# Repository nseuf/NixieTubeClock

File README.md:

# NixieTubeClock
NixieTubeClock is a GPS-based desk clock that is precise up to 10ms, and uses nixie tubes to display the time.

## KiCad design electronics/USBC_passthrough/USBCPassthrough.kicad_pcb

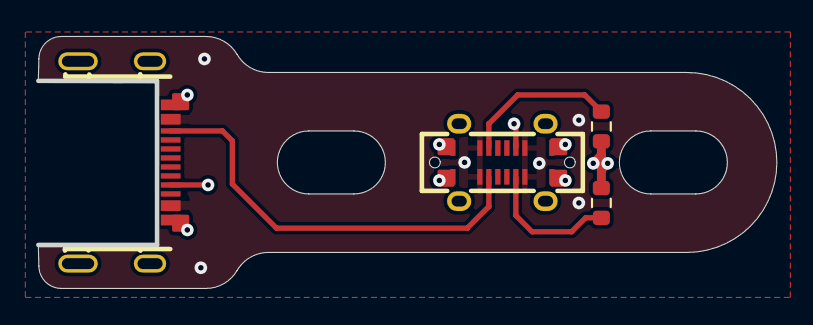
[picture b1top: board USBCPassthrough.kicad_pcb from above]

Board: 4 copper layers, 40.9 x 13.8 mm, 4 parts (0 on the bottom side), 6 nets.

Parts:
J1: USB_C_Receptacle_USB2.0_16P; TYPE-C-SMD_USB4120-03-C
J2: USB_C_Receptacle_USB2.0_16P; USB-C-SMD_TYPEC-302-BRP16SC16
R1, R2: 5k1; R_0603_1608Metric

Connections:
+5V: J1.A4 (VBUS), J1.A9 (VBUS), J1.B4 (VBUS), J1.B9 (VBUS), J2.A4 (VBUS), J2.B4 (VBUS)
GND: J1.A1 (GND), J1.A12 (GND), J1.B1 (GND), J1.B12 (GND), J1.S1 (SHIELD), J2.A1 (GND), J2.B1 (GND), J2.S1 (SHIELD), R1.2, R2.2
unnamed: J1.A5 (CC1), R2.1
unnamed: J1.B5 (CC2), R1.1
unnamed: J1.A8 (SBU1), J2.A8 (SBU1)
unnamed: J1.B8 (SBU2), J2.B8 (SBU2)

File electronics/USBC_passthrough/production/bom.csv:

Designator,Footprint,Quantity,Value,LCSC Part #
J1,TYPE-C-SMD_USB4120-03-C,1,USB_C_Receptacle_USB2.0_16P,
J2,USB-C-SMD_TYPEC-302-BRP16SC16,1,USB_C_Receptacle_USB2.0_16P,

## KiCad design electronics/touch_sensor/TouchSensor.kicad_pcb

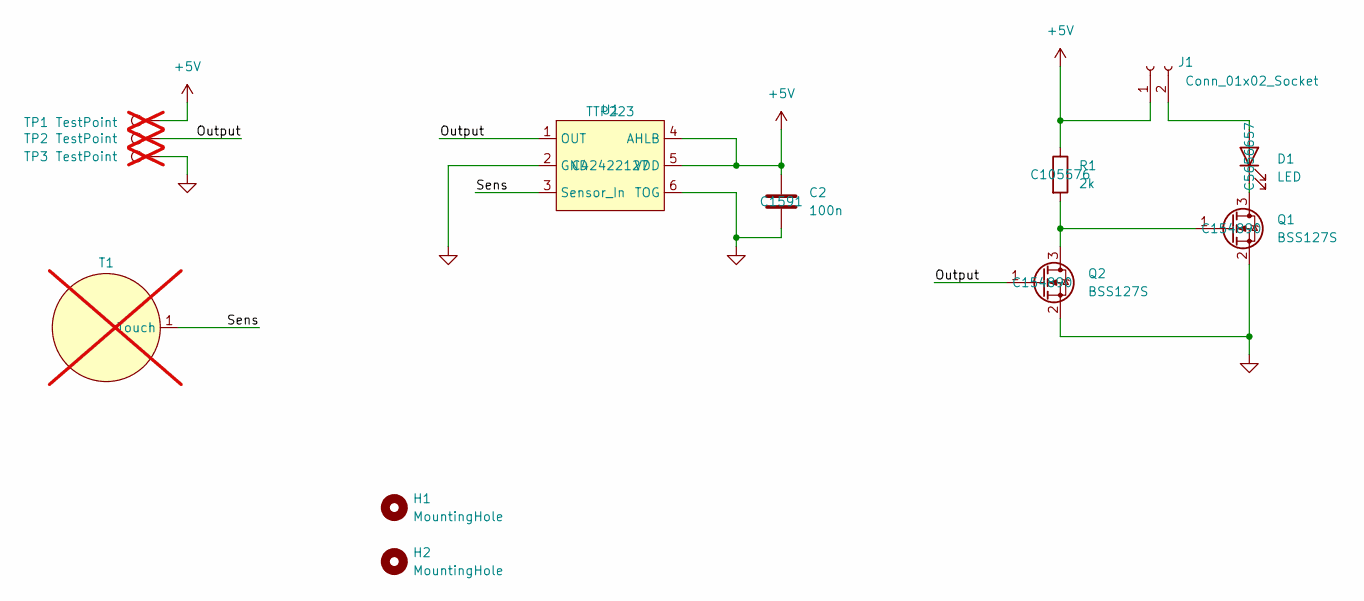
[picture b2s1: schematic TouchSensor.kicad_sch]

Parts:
C2: 100n; C_0603_1608Metric; LCSC_Part# C1591
D1: LED; D_0603_1608Metric; LCSC_Part# C5656657
H1, H2: MountingHole; MountingHole_2.2mm_M2_ISO7380
J1: Conn_01x02_Socket; JST_SUR_BM02B-SURS-TF_1x02-1MP_P0.80mm_Vertical
Q1, Q2: BSS127S; SOT-23; LCSC_Part# C154890
R1: 2k; R_0603_1608Metric; LCSC_Part# C105576
T1: TouchPad; not fitted
TP1, TP2, TP3: TestPoint; TestPoint_THTPad_D2.5mm_Drill1.2mm; not fitted
U1: TTP223; SOT-23-6; LCSC_Part# C42422127

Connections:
+5V: C2.1, J1.1, R1.1, TP1.1, U1.4 (AHLB), U1.5 (VDD)
/Output: Q2.1 (G), TP2.1, U1.1 (OUT)
/Sens: T1.1 (Touch), U1.3 (Sensor_In)
GND: C2.2, Q1.2 (S), Q2.2 (S), TP3.1, U1.2 (GND), U1.6 (TOG)
unnamed: D1.2 (A), J1.2
unnamed: D1.1 (K), Q1.3 (D)
unnamed: Q1.1 (G), Q2.3 (D), R1.2

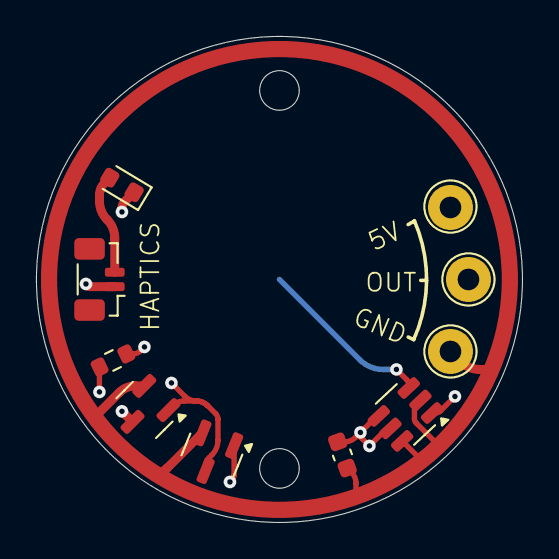
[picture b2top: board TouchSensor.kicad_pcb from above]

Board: 4 copper layers, 27.0 x 27.0 mm, 13 parts (1 on the bottom side), 7 nets.

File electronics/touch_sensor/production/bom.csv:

Designator,Footprint,Quantity,Value,LCSC Part #
C2,0603,1,100n,
D1,0603,1,LED,
J1,JST_SUR_BM02B-SURS-TF_1x02-1MP_P0.80mm_Vertical,1,Conn_01x02_Socket,
"Q1, Q2",SOT-23,2,BSS127S,
R1,0603,1,2k,
U1,SOT-23-6,1,TTP223,

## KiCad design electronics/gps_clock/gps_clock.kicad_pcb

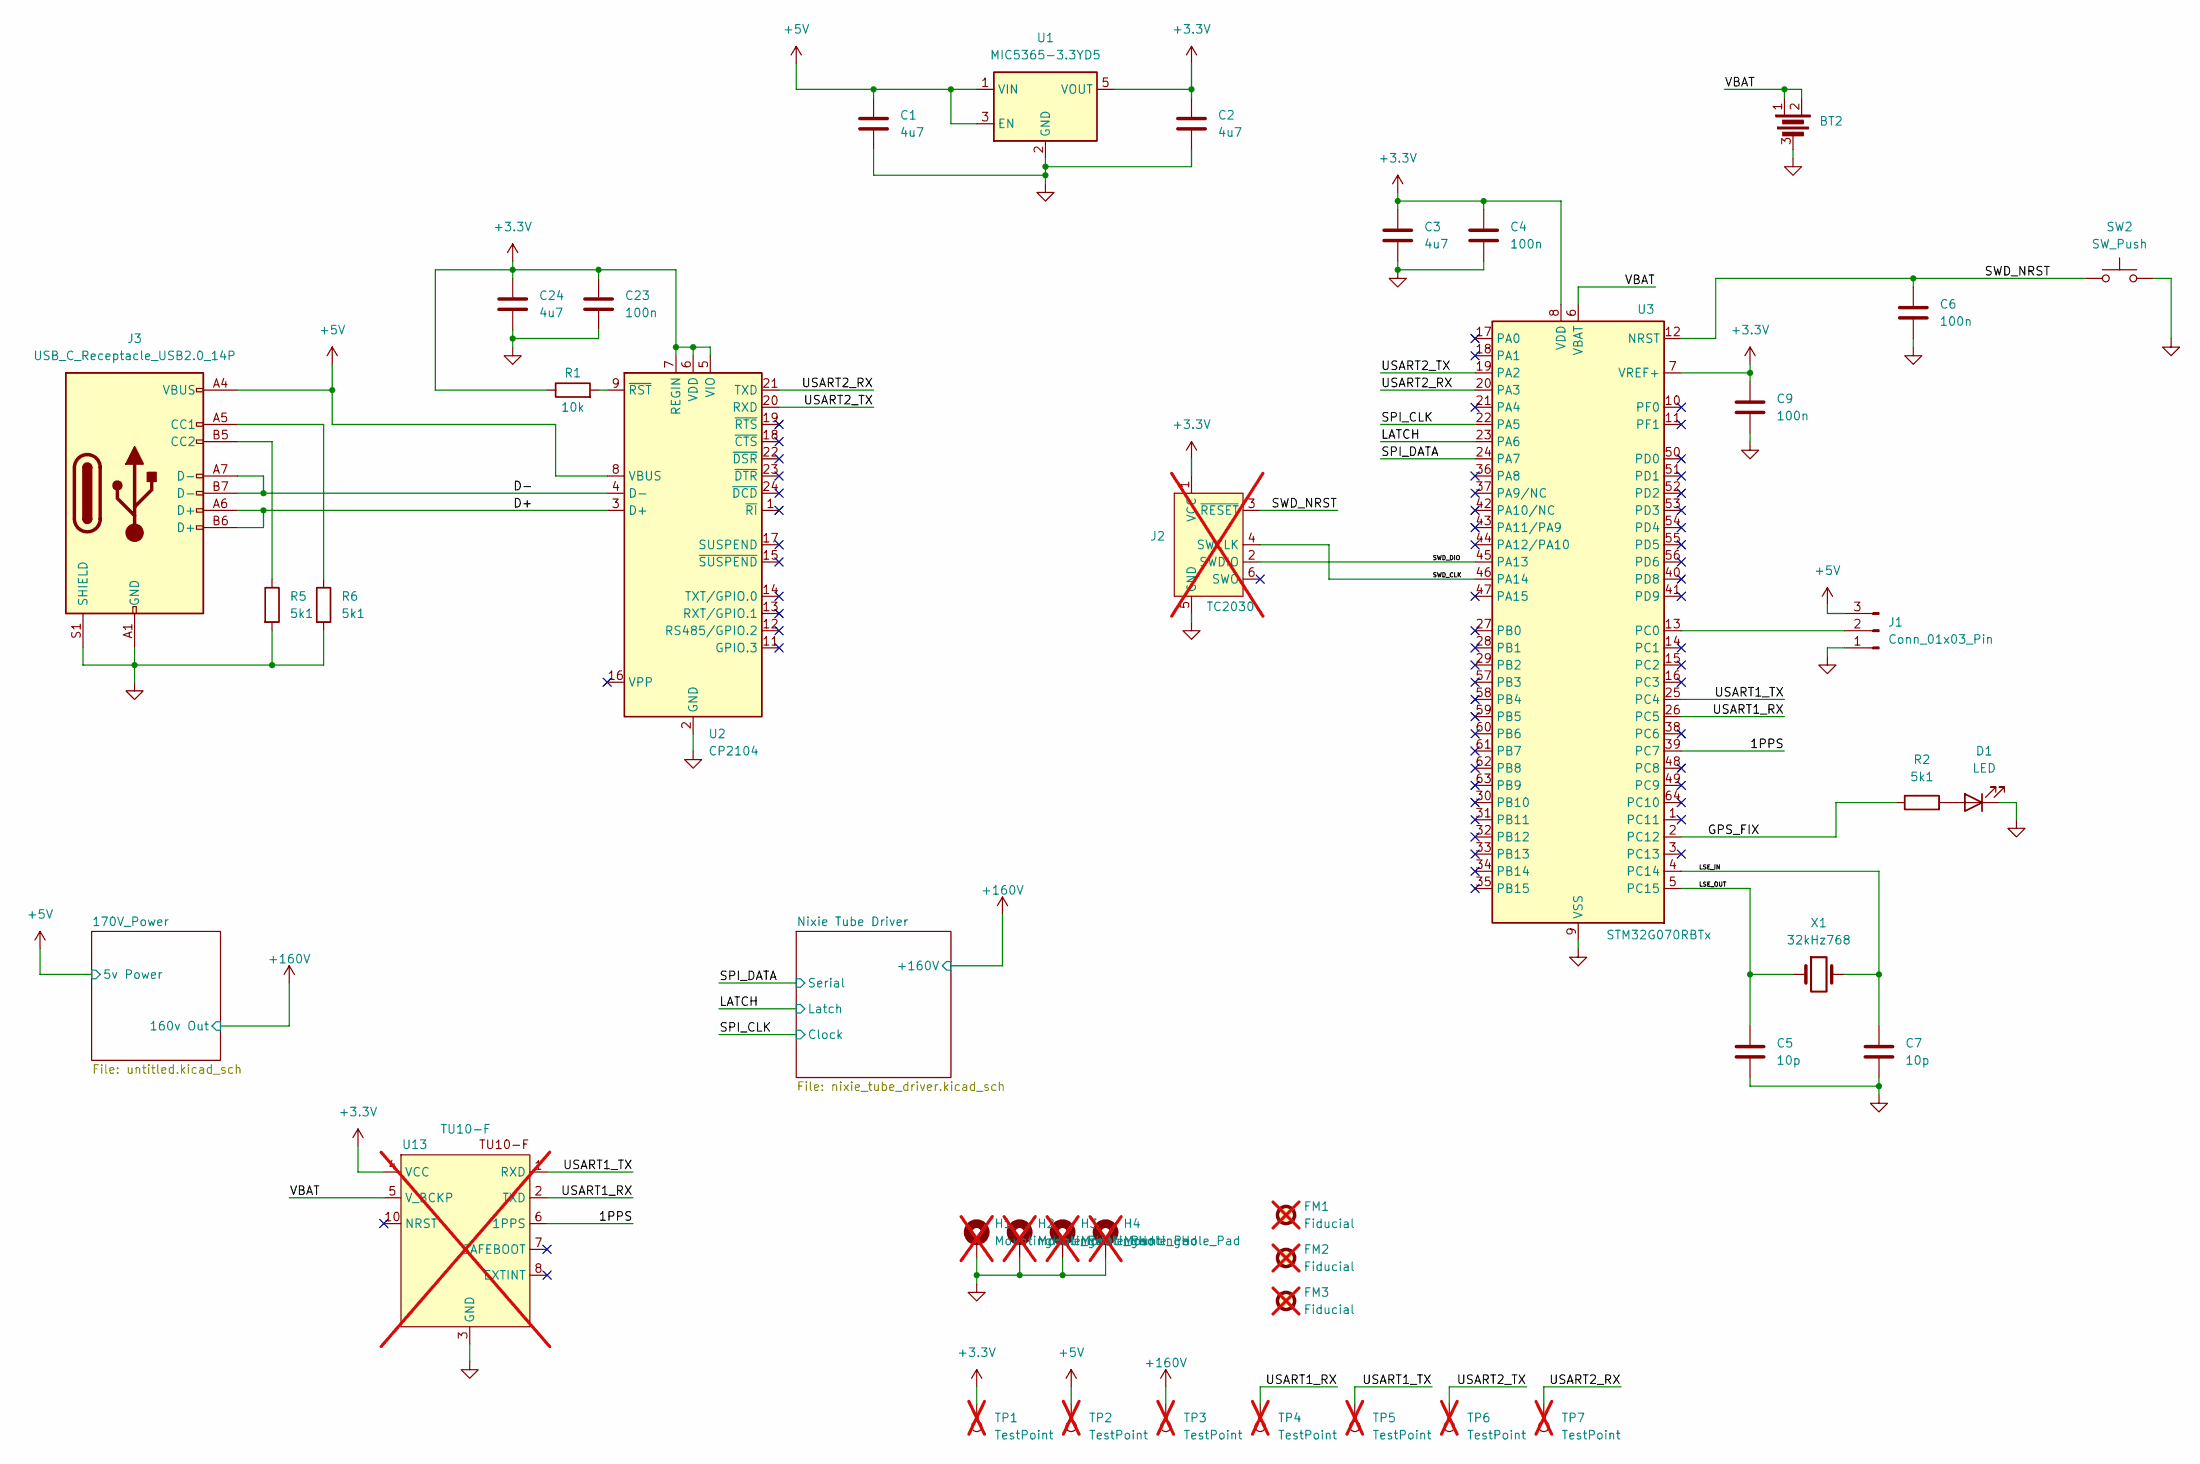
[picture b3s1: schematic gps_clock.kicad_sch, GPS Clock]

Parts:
BT2: BAT-SMD_MY-1220-03; LCSC_Part# C20606802
C1, C2, C3, C24: 4u7; C_0603_1608Metric; MFR_Part# CL10A475KP8NNNC; LCSC_Part# C1705
C4, C6, C9, C23: 100n; C_0402_1005Metric; MFR_Part# CL05B104KO5NNNC; LCSC_Part# C1525
C5, C7: 10p; C_0402_1005Metric; MFR_Part# 0402CG100J500NT; LCSC_Part# C1545
D1: LED; D_0603_1608Metric; LCSC_Part# C5656657
FM1, FM2, FM3: Fiducial; Fiducial_1mm_Mask2mm; not fitted
H1, H2, H3, H4: MountingHole_Pad; MountingHole_3mm_Pad_Via; not fitted
J1: Conn_01x03_Pin; Molex_PicoBlade_53261-0371_1x03-1MP_P1.25mm_Horizontal; LCSC_Part# C293630
J2: TC2030; Tag-Connect_TC2030-IDC-FP_2x03_P1.27mm_Vertical; MFR_Part# N/A; LCSC_Part# N/A; not fitted
J3: USB_C_Receptacle_USB2.0_14P; USB-C-SMD_U263-241N-4BQC02; LCSC_Part# C2689742
R1: 10k; R_0603_1608Metric; MFR_Part# 0402WGF5101TCE; LCSC_Part# C15401
R2, R5, R6: 5k1; R_0402_1005Metric; MFR_Part# 0402WGF5101TCE; LCSC_Part# C25905
SW2: SW_Push; SW_Push_1P1T_XKB_TS-1187A; MFR_Part# TS-1187A-B-A-B; LCSC_Part# C318884
TP1, TP2, TP3, TP4, TP5, TP6, TP7: TestPoint; TestPoint_Pad_D2.5mm; LCSC_Part# N/A; not fitted
U1: MIC5365-3.3YD5; SOT-23-5; MFR_Part# MIC5365-3.3YD5-TR; LCSC_Part# C626098
U2: CP2104; QFN-24-1EP_4x4mm_P0.5mm_EP2.7x2.7mm; LCSC_Part# C47742
U3: STM32G070RBTx; LQFP-64_10x10mm_P0.5mm; MFR_Part# STM32G070RBT6; LCSC_Part# C529340
U13: TU10-F; LCSC_Part# N/A; not fitted
X1: 32kHz768; Crystal_SMD_2012-2Pin_2.0x1.2mm; MFR_Part# NX2012SA-32.768KHZ-EXS00A-MU00644; LCSC_Part# C2828558

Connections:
+3.3V: C2.1, C3.1, C4.1, C9.1, C23.1, C24.1, J2.1 (VCC), R1.1, TP1.1, U1.5 (VOUT), U2.5 (VIO), U2.6 (VDD), U2.7 (REGIN), U3.7 (VREF+), U3.8 (VDD), U13.4 (VCC)
+5V: C1.1, J1.3, J3.A4 (VBUS), J3.A9 (VBUS), J3.B4 (VBUS), J3.B9 (VBUS), TP2.1, U1.1 (VIN), U1.3 (EN), U2.8 (VBUS); also elsewhere on the board
+160V: TP3.1; also elsewhere on the board
/1PPS: U3.39 (PC7), U13.6 (1PPS)
/D+: J3.A6 (D+), J3.B6 (D+), U2.3 (D+)
/D-: J3.A7 (D-), J3.B7 (D-), U2.4 (D-)
/GPS_FIX: R2.1, U3.2 (PC12)
/LATCH: U3.23 (PA6); also elsewhere on the board
/LSE_IN: C7.1, U3.4 (PC14), X1.2
/LSE_OUT: C5.1, U3.5 (PC15), X1.1
/SPI_CLK: U3.22 (PA5); also elsewhere on the board
/SPI_DATA: U3.24 (PA7); also elsewhere on the board
/SWD_CLK: J2.4 (SWCLK), U3.46 (PA14)
/SWD_DIO: J2.2 (SWDIO), U3.45 (PA13)
/SWD_NRST: C6.1, J2.3 (~RESET), SW2.1, U3.12 (NRST)
/USART1_RX: TP4.1, U3.26 (PC5), U13.2 (TXD)
/USART1_TX: TP5.1, U3.25 (PC4), U13.1 (RXD)
/USART2_RX: TP7.1, U2.21 (TXD), U3.20 (PA3)
/USART2_TX: TP6.1, U2.20 (RXD), U3.19 (PA2)
/VBAT: BT2.1, BT2.2, U3.6 (VBAT), U13.5 (V_BCKP)
GND: BT2.3, C1.2, C2.2, C3.2, C4.2, C5.2, C6.2, C7.2, C9.2, C23.2, C24.2, D1.1 (K), H1.1, H2.1, H3.1, H4.1, J1.1, J2.5 (GND), J3.A1 (GND), J3.A12 (GND), J3.B1 (GND), J3.B12 (GND), J3.S1 (SHIELD), R5.2, R6.2, SW2.2, U1.2 (GND), U2.2 (GND), U2.25 (GND), U3.9 (VSS), U13.3 (GND), U13.12 (GND); also elsewhere on the board
unnamed: D1.2 (A), R2.2
unnamed: J1.2, U3.13 (PC0)
unnamed: J3.A5 (CC1), R6.1
unnamed: J3.B5 (CC2), R5.1
unnamed: R1.2, U2.9 (~RST)

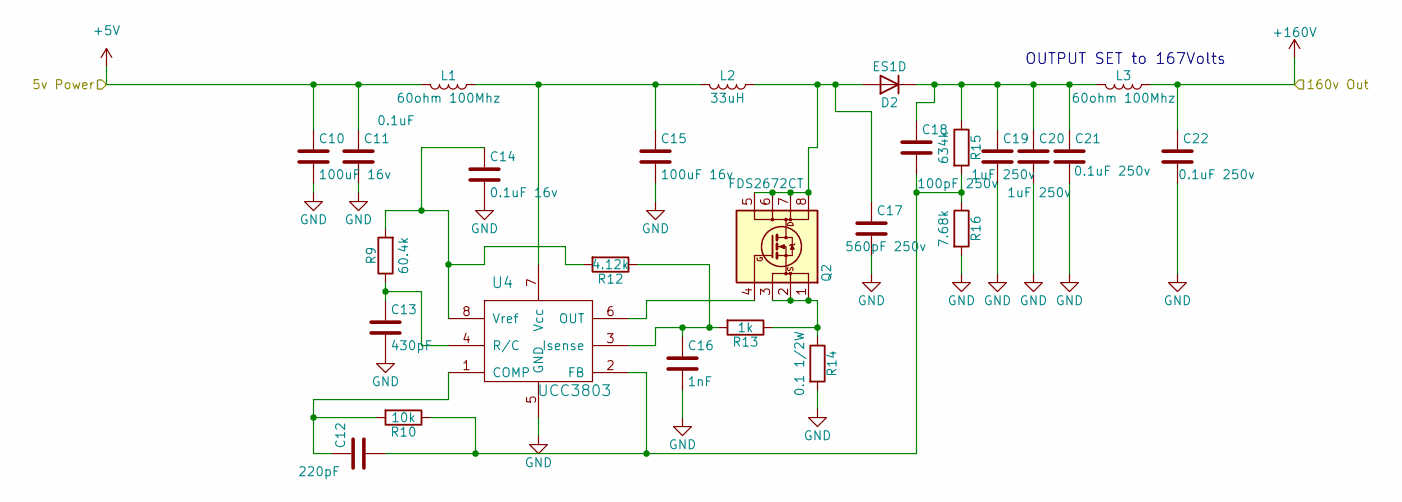
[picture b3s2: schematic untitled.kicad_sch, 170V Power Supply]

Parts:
C10, C15: 100uF 16v; C_1210_3225Metric; MPN EMK325ABJ107MM-P; LCSC_Part# C90143
C11: 0.1uF; C_0805_2012Metric; MPN C0805C104K3RACTU; LCSC_Part# C1852967
C12: 220pF; C_0805_2012Metric; MPN C0805C221M5RACTU; LCSC_Part# C1727
C13: 430pF; C_0805_2012Metric; MPN CL21C431JBANNNC; LCSC_Part# C67898
C14: 0.1uF 16v; C_0805_2012Metric; MPN C0805C104K3RACTU; LCSC_Part# C519980
C16: 1nF; C_0805_2012Metric; MPN C0805C102M5RACTU; LCSC_Part# C46553
C17: 560pF 250v; C_0805_2012Metric; MPN C0603C561JAGAC7867; LCSC_Part# C113870
C18: 100pF 250v; C_0805_2012Metric; MPN C0805C101JAGAC7800; LCSC_Part# C2929108
C19, C20: 1uF 250v; C_1812_4532Metric; MPN C4532X7T2E105M250KE; LCSC_Part# C106152
C21, C22: 0.1uF 250v; C_0805_2012Metric; MPN CGA4J3X7T2E104M125AE; LCSC_Part# C5451689
D2: ES1D; D_SMA; MPN ES1D; LCSC_Part# C84602
L1, L3: 60ohm 100Mhz; R_0805_2012Metric; MPN BKP2125HS600-T; LCSC_Part# C44362
L2: 33uH; WE-PD_1210; MPN 7447709330; LCSC_Part# C2651182
Q2: FDS2672CT; SOIC-8_3.9x4.9mm_P1.27mm; MPN FDS2672CT-ND; LCSC_Part# C463724
R9: 60.4k; R_0805_2012Metric; MPN RC0805FR-0760K4L; LCSC_Part# C218645
R10: 10k; R_0603_1608Metric; MFR_Part# 0603WAJ0103T5E; LCSC_Part# C15401
R12: 4.12k; R_0805_2012Metric; MPN RC0805FR-074K12L; LCSC_Part# C218607
R13: 1k; R_0805_2012Metric; MPN RC0805FR-071KL; LCSC_Part# C17513
R14: 0.1 1/2W; R_0805_2012Metric; MPN ERJ-6DSFR10V; LCSC_Part# C2935234
R15: 634k; R_0805_2012Metric; MPN RC0805FR-07634KL; LCSC_Part# C237126
R16: 7.68k; R_0805_2012Metric; MPN RC0805FR-077K68L; LCSC_Part# C30041
U4: UCC3803; D0008A_L; MPN UCC3803DTR; LCSC_Part# C2657971

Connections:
+5V: C10.1, C11.1, L1.2; also elsewhere on the board
+160V: C22.1, L3.1; also elsewhere on the board
GND: C10.2, C11.2, C13.2, C14.2, C15.2, C16.2, C17.2, C19.2, C20.2, C21.2, C22.2, R14.2, R16.2, U4.5 (GND); also elsewhere on the board
unnamed: C17.1, D2.2 (A), L2.1, Q2.5 (D), Q2.6 (D), Q2.7 (D), Q2.8 (D)
unnamed: C18.1, C19.1, C20.1, C21.1, D2.1 (K), L3.2, R15.1
unnamed: Q2.4 (G), U4.6 (OUT)
unnamed: Q2.1 (S), Q2.2 (S), Q2.3 (S), R13.1, R14.1
unnamed: C12.1, R10.2, U4.1 (COMP)
unnamed: C12.2, C18.2, R10.1, R15.2, R16.1, U4.2 (FB)
unnamed: C16.1, R12.1, R13.2, U4.3 (Isense)
unnamed: C13.1, R9.1, U4.4 (R/C)
unnamed: C15.1, L1.1, L2.2, U4.7 (Vcc)
unnamed: C14.1, R9.2, R12.2, U4.8 (Vref)

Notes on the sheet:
OUTPUT SET to 167Volts

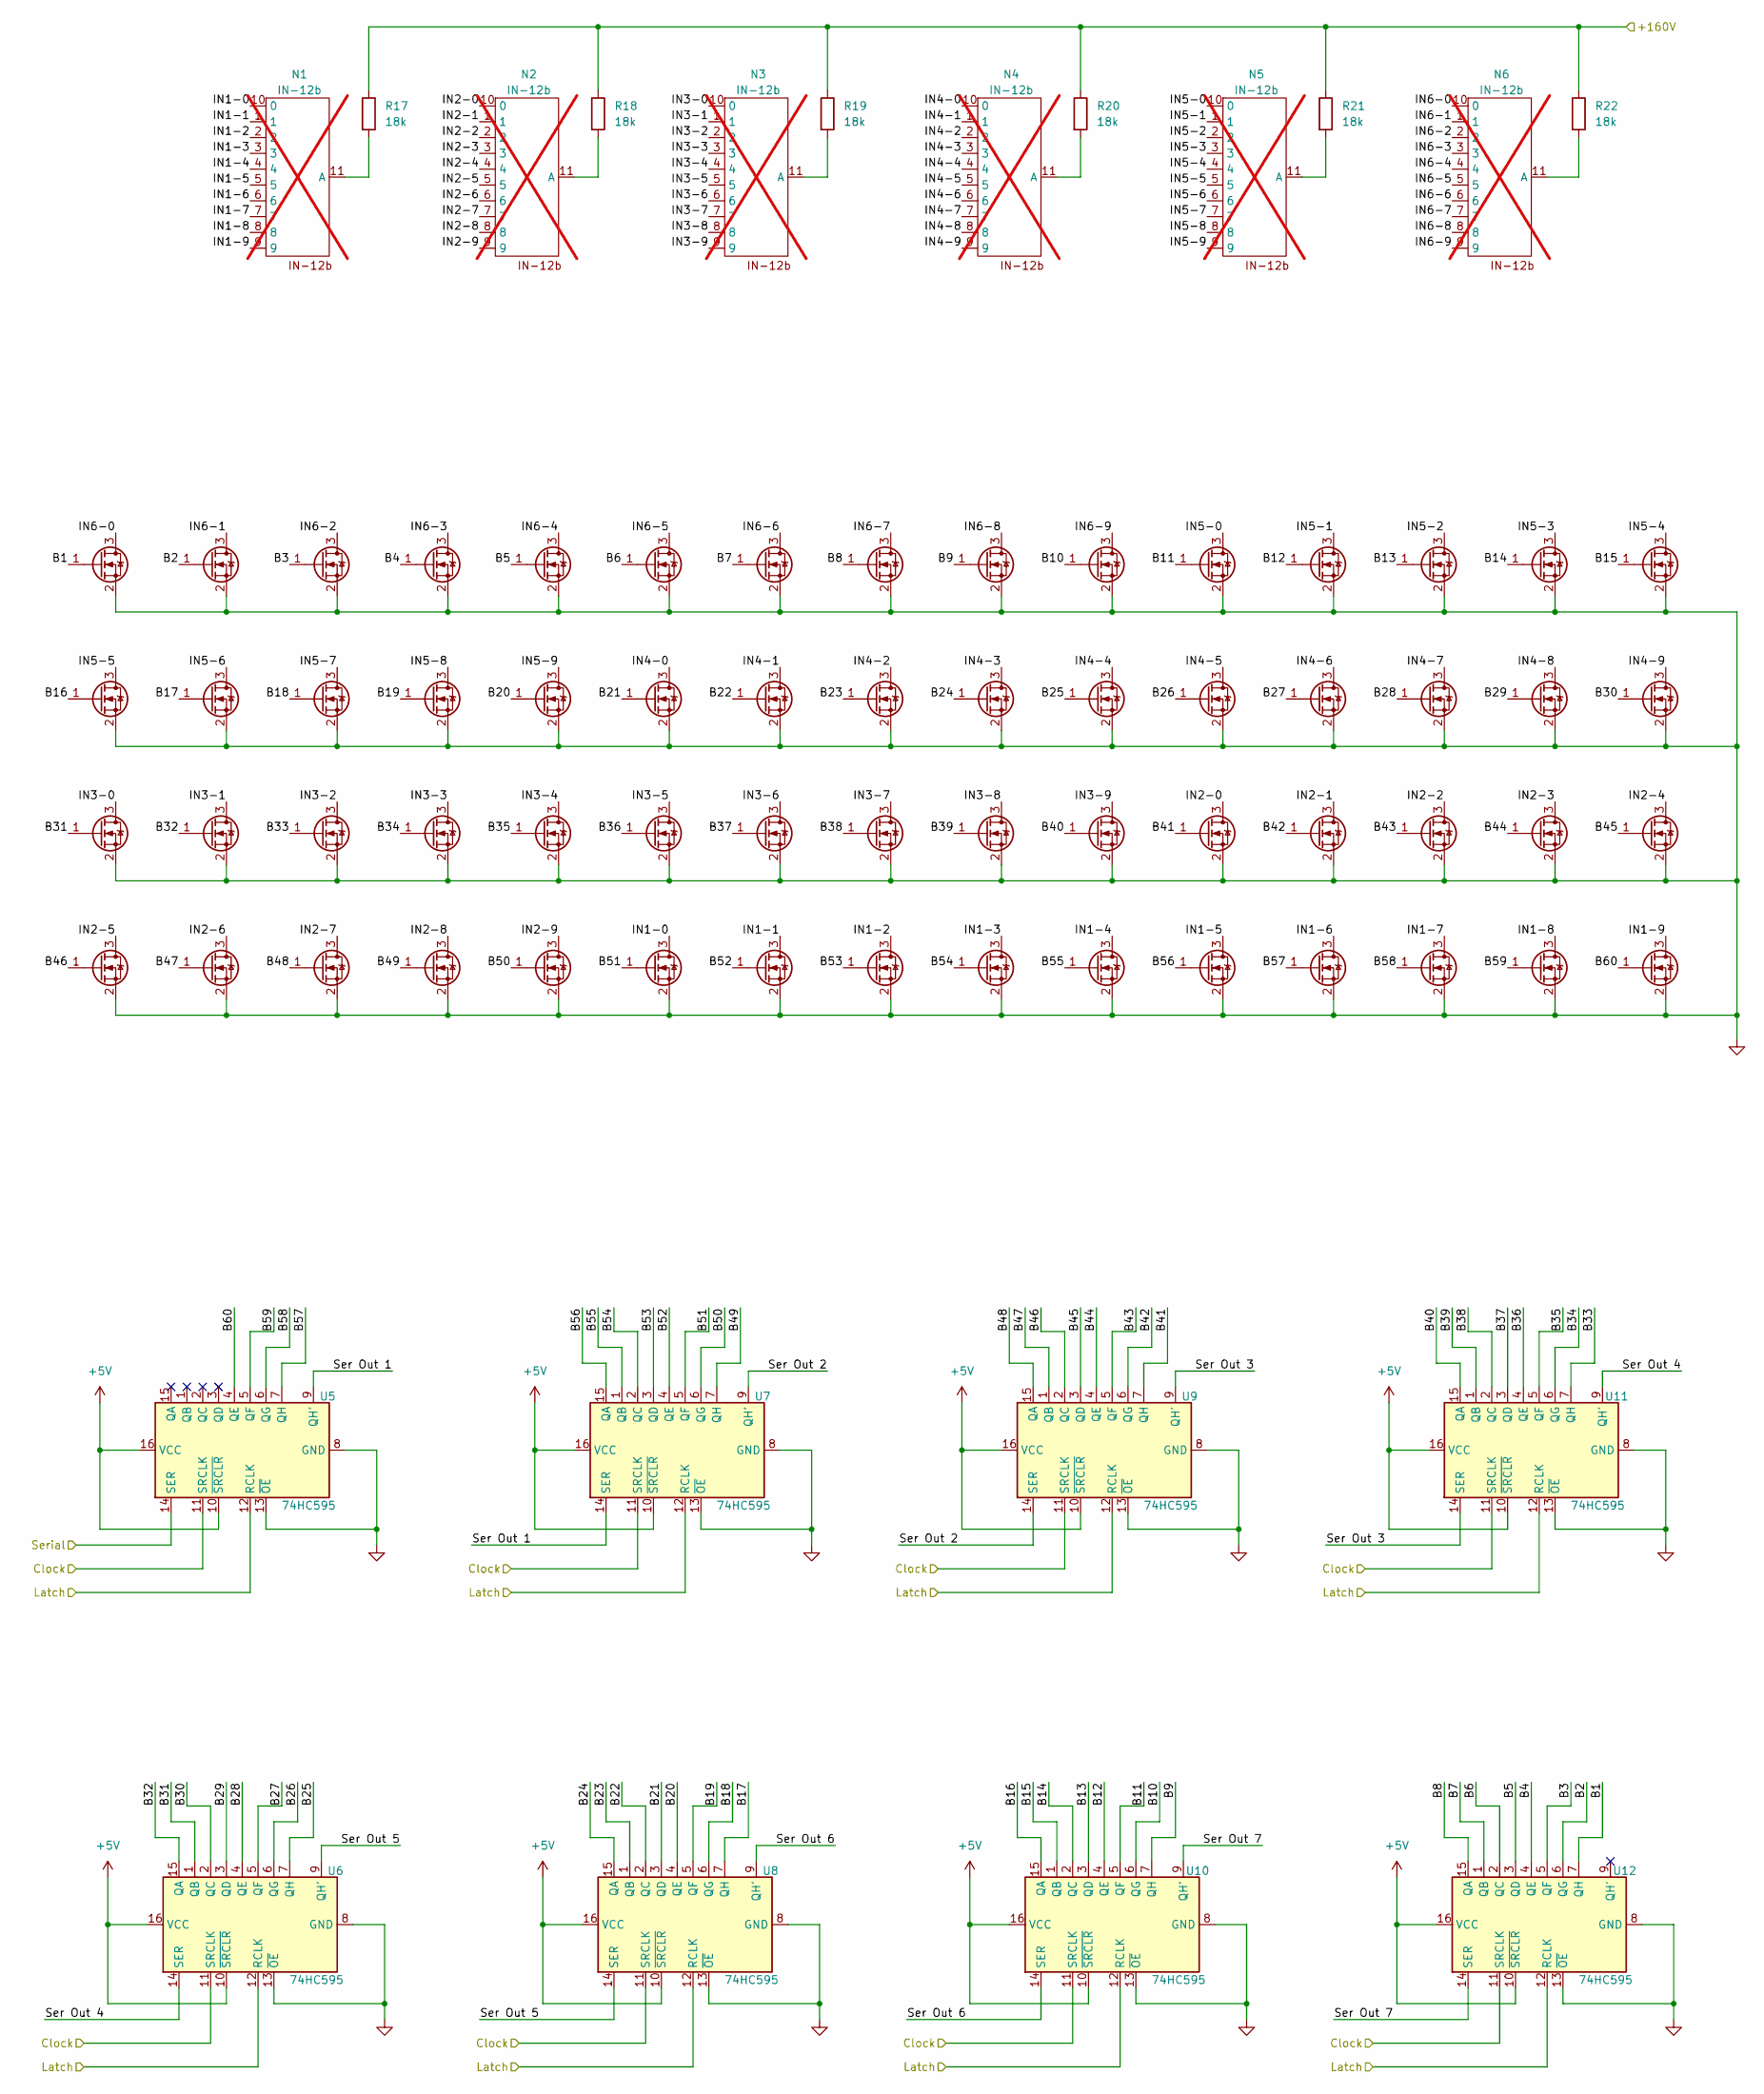
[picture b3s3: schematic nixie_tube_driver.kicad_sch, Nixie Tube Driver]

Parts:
N1, N2, N3, N4, N5, N6: IN-12b; MFR_Part# IN-12b; LCSC_Part# N/A; not fitted
Q3, Q4, Q5, Q6, Q7, Q8, Q9, Q10, Q11, Q12, Q13, Q14, Q15, Q16, Q17, Q18, Q19, Q20, Q21, Q22, Q23, Q24, Q25, Q26, Q27, Q28, Q29, Q30, Q31, Q32, Q33, Q34, Q35, Q36, Q37, Q38, Q39, Q40, Q41, Q42, Q43, Q44, Q45, Q46, Q47, Q48, Q49, Q50, Q51, Q52, Q53, Q54, Q55, Q56, Q57, Q58, Q59, Q60, Q61, Q62: BSS127S; SOT-23; MFR_Part# BSS127S-7; LCSC_Part# C154890
R17, R18, R19, R20, R21, R22: 18k; R_1812_4532Metric; MFR_Part# 181207F1802T4E; LCSC_Part# C422140
U5, U6, U7, U8, U9, U10, U11, U12: 74HC595; SOIC-16W_5.3x10.2mm_P1.27mm; MFR_Part# 74HC595; LCSC_Part# C18164493

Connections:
+5V: U5.10 (~SRCLR), U5.16 (VCC), U6.10 (~SRCLR), U6.16 (VCC), U7.10 (~SRCLR), U7.16 (VCC), U8.10 (~SRCLR), U8.16 (VCC), U9.10 (~SRCLR), U9.16 (VCC), U10.10 (~SRCLR), U10.16 (VCC), U11.10 (~SRCLR), U11.16 (VCC), U12.10 (~SRCLR), U12.16 (VCC); also elsewhere on the board
+160V: R17.1, R18.1, R19.1, R20.1, R21.1, R22.1; also elsewhere on the board
/LATCH: U5.12 (RCLK), U6.12 (RCLK), U7.12 (RCLK), U8.12 (RCLK), U9.12 (RCLK), U10.12 (RCLK), U11.12 (RCLK), U12.12 (RCLK); also elsewhere on the board
/Nixie Tube Driver/B1: Q3.1 (G), U12.7 (QH)
/Nixie Tube Driver/B2: Q7.1 (G), U12.6 (QG)
/Nixie Tube Driver/B3: Q11.1 (G), U12.5 (QF)
/Nixie Tube Driver/B4: Q15.1 (G), U12.4 (QE)
/Nixie Tube Driver/B5: Q19.1 (G), U12.3 (QD)
/Nixie Tube Driver/B6: Q23.1 (G), U12.2 (QC)
/Nixie Tube Driver/B7: Q27.1 (G), U12.1 (QB)
/Nixie Tube Driver/B8: Q31.1 (G), U12.15 (QA)
/Nixie Tube Driver/B9: Q35.1 (G), U10.7 (QH)
/Nixie Tube Driver/B10: Q39.1 (G), U10.6 (QG)
/Nixie Tube Driver/B11: Q43.1 (G), U10.5 (QF)
/Nixie Tube Driver/B12: Q47.1 (G), U10.4 (QE)
/Nixie Tube Driver/B13: Q51.1 (G), U10.3 (QD)
/Nixie Tube Driver/B14: Q55.1 (G), U10.2 (QC)
/Nixie Tube Driver/B15: Q59.1 (G), U10.1 (QB)
/Nixie Tube Driver/B16: Q4.1 (G), U10.15 (QA)
/Nixie Tube Driver/B17: Q8.1 (G), U8.7 (QH)
/Nixie Tube Driver/B18: Q12.1 (G), U8.6 (QG)
/Nixie Tube Driver/B19: Q16.1 (G), U8.5 (QF)
/Nixie Tube Driver/B20: Q20.1 (G), U8.4 (QE)
/Nixie Tube Driver/B21: Q24.1 (G), U8.3 (QD)
/Nixie Tube Driver/B22: Q28.1 (G), U8.2 (QC)
/Nixie Tube Driver/B23: Q32.1 (G), U8.1 (QB)
/Nixie Tube Driver/B24: Q36.1 (G), U8.15 (QA)
/Nixie Tube Driver/B25: Q40.1 (G), U6.7 (QH)
/Nixie Tube Driver/B26: Q44.1 (G), U6.6 (QG)
/Nixie Tube Driver/B27: Q48.1 (G), U6.5 (QF)
/Nixie Tube Driver/B28: Q52.1 (G), U6.4 (QE)
/Nixie Tube Driver/B29: Q56.1 (G), U6.3 (QD)
/Nixie Tube Driver/B30: Q60.1 (G), U6.2 (QC)
/Nixie Tube Driver/B31: Q5.1 (G), U6.1 (QB)
/Nixie Tube Driver/B32: Q9.1 (G), U6.15 (QA)
/Nixie Tube Driver/B33: Q13.1 (G), U11.7 (QH)
/Nixie Tube Driver/B34: Q17.1 (G), U11.6 (QG)
/Nixie Tube Driver/B35: Q21.1 (G), U11.5 (QF)
/Nixie Tube Driver/B36: Q25.1 (G), U11.4 (QE)
/Nixie Tube Driver/B37: Q29.1 (G), U11.3 (QD)
/Nixie Tube Driver/B38: Q33.1 (G), U11.2 (QC)
/Nixie Tube Driver/B39: Q37.1 (G), U11.1 (QB)
/Nixie Tube Driver/B40: Q41.1 (G), U11.15 (QA)
/Nixie Tube Driver/B41: Q45.1 (G), U9.7 (QH)
/Nixie Tube Driver/B42: Q49.1 (G), U9.6 (QG)
/Nixie Tube Driver/B43: Q53.1 (G), U9.5 (QF)
/Nixie Tube Driver/B44: Q57.1 (G), U9.4 (QE)
/Nixie Tube Driver/B45: Q61.1 (G), U9.3 (QD)
/Nixie Tube Driver/B46: Q6.1 (G), U9.2 (QC)
/Nixie Tube Driver/B47: Q10.1 (G), U9.1 (QB)
/Nixie Tube Driver/B48: Q14.1 (G), U9.15 (QA)
/Nixie Tube Driver/B49: Q18.1 (G), U7.7 (QH)
/Nixie Tube Driver/B50: Q22.1 (G), U7.6 (QG)
/Nixie Tube Driver/B51: Q26.1 (G), U7.5 (QF)
/Nixie Tube Driver/B52: Q30.1 (G), U7.4 (QE)
/Nixie Tube Driver/B53: Q34.1 (G), U7.3 (QD)
/Nixie Tube Driver/B54: Q38.1 (G), U7.2 (QC)
/Nixie Tube Driver/B55: Q42.1 (G), U7.1 (QB)
/Nixie Tube Driver/B56: Q46.1 (G), U7.15 (QA)
/Nixie Tube Driver/B57: Q50.1 (G), U5.7 (QH)
/Nixie Tube Driver/B58: Q54.1 (G), U5.6 (QG)
/Nixie Tube Driver/B59: Q58.1 (G), U5.5 (QF)
/Nixie Tube Driver/B60: Q62.1 (G), U5.4 (QE)
/Nixie Tube Driver/IN1-0: N1.10 (0), Q26.3 (D)
/Nixie Tube Driver/IN1-1: N1.1, Q30.3 (D)
/Nixie Tube Driver/IN1-2: N1.2, Q34.3 (D)
/Nixie Tube Driver/IN1-3: N1.3, Q38.3 (D)
/Nixie Tube Driver/IN1-4: N1.4, Q42.3 (D)
/Nixie Tube Driver/IN1-5: N1.5, Q46.3 (D)
/Nixie Tube Driver/IN1-6: N1.6, Q50.3 (D)
/Nixie Tube Driver/IN1-7: N1.7, Q54.3 (D)
/Nixie Tube Driver/IN1-8: N1.8, Q58.3 (D)
/Nixie Tube Driver/IN1-9: N1.9, Q62.3 (D)
/Nixie Tube Driver/IN2-0: N2.10 (0), Q45.3 (D)
/Nixie Tube Driver/IN2-1: N2.1, Q49.3 (D)
/Nixie Tube Driver/IN2-2: N2.2, Q53.3 (D)
/Nixie Tube Driver/IN2-3: N2.3, Q57.3 (D)
/Nixie Tube Driver/IN2-4: N2.4, Q61.3 (D)
/Nixie Tube Driver/IN2-5: N2.5, Q6.3 (D)
/Nixie Tube Driver/IN2-6: N2.6, Q10.3 (D)
/Nixie Tube Driver/IN2-7: N2.7, Q14.3 (D)
/Nixie Tube Driver/IN2-8: N2.8, Q18.3 (D)
/Nixie Tube Driver/IN2-9: N2.9, Q22.3 (D)
/Nixie Tube Driver/IN3-0: N3.10 (0), Q5.3 (D)
/Nixie Tube Driver/IN3-1: N3.1, Q9.3 (D)
/Nixie Tube Driver/IN3-2: N3.2, Q13.3 (D)
/Nixie Tube Driver/IN3-3: N3.3, Q17.3 (D)
/Nixie Tube Driver/IN3-4: N3.4, Q21.3 (D)
/Nixie Tube Driver/IN3-5: N3.5, Q25.3 (D)
/Nixie Tube Driver/IN3-6: N3.6, Q29.3 (D)
/Nixie Tube Driver/IN3-7: N3.7, Q33.3 (D)
/Nixie Tube Driver/IN3-8: N3.8, Q37.3 (D)
/Nixie Tube Driver/IN3-9: N3.9, Q41.3 (D)
/Nixie Tube Driver/IN4-0: N4.10 (0), Q24.3 (D)
/Nixie Tube Driver/IN4-1: N4.1, Q28.3 (D)
/Nixie Tube Driver/IN4-2: N4.2, Q32.3 (D)
/Nixie Tube Driver/IN4-3: N4.3, Q36.3 (D)
/Nixie Tube Driver/IN4-4: N4.4, Q40.3 (D)
/Nixie Tube Driver/IN4-5: N4.5, Q44.3 (D)
/Nixie Tube Driver/IN4-6: N4.6, Q48.3 (D)
/Nixie Tube Driver/IN4-7: N4.7, Q52.3 (D)
/Nixie Tube Driver/IN4-8: N4.8, Q56.3 (D)
/Nixie Tube Driver/IN4-9: N4.9, Q60.3 (D)
/Nixie Tube Driver/IN5-0: N5.10 (0), Q43.3 (D)
/Nixie Tube Driver/IN5-1: N5.1, Q47.3 (D)
/Nixie Tube Driver/IN5-2: N5.2, Q51.3 (D)
/Nixie Tube Driver/IN5-3: N5.3, Q55.3 (D)
/Nixie Tube Driver/IN5-4: N5.4, Q59.3 (D)
/Nixie Tube Driver/IN5-5: N5.5, Q4.3 (D)
/Nixie Tube Driver/IN5-6: N5.6, Q8.3 (D)
/Nixie Tube Driver/IN5-7: N5.7, Q12.3 (D)
/Nixie Tube Driver/IN5-8: N5.8, Q16.3 (D)
/Nixie Tube Driver/IN5-9: N5.9, Q20.3 (D)
/Nixie Tube Driver/IN6-0: N6.10 (0), Q3.3 (D)
/Nixie Tube Driver/IN6-1: N6.1, Q7.3 (D)
/Nixie Tube Driver/IN6-2: N6.2, Q11.3 (D)
/Nixie Tube Driver/IN6-3: N6.3, Q15.3 (D)
/Nixie Tube Driver/IN6-4: N6.4, Q19.3 (D)
/Nixie Tube Driver/IN6-5: N6.5, Q23.3 (D)
/Nixie Tube Driver/IN6-6: N6.6, Q27.3 (D)
/Nixie Tube Driver/IN6-7: N6.7, Q31.3 (D)
/Nixie Tube Driver/IN6-8: N6.8, Q35.3 (D)
/Nixie Tube Driver/IN6-9: N6.9, Q39.3 (D)
/Nixie Tube Driver/Ser Out 1: U5.9 (QH'), U7.14 (SER)
/Nixie Tube Driver/Ser Out 2: U7.9 (QH'), U9.14 (SER)
/Nixie Tube Driver/Ser Out 3: U9.9 (QH'), U11.14 (SER)
/Nixie Tube Driver/Ser Out 4: U6.14 (SER), U11.9 (QH')
/Nixie Tube Driver/Ser Out 5: U6.9 (QH'), U8.14 (SER)
/Nixie Tube Driver/Ser Out 6: U8.9 (QH'), U10.14 (SER)
/Nixie Tube Driver/Ser Out 7: U10.9 (QH'), U12.14 (SER)
/SPI_CLK: U5.11 (SRCLK), U6.11 (SRCLK), U7.11 (SRCLK), U8.11 (SRCLK), U9.11 (SRCLK), U10.11 (SRCLK), U11.11 (SRCLK), U12.11 (SRCLK); also elsewhere on the board
/SPI_DATA: U5.14 (SER); also elsewhere on the board
GND: Q3.2 (S), Q4.2 (S), Q5.2 (S), Q6.2 (S), Q7.2 (S), Q8.2 (S), Q9.2 (S), Q10.2 (S), Q11.2 (S), Q12.2 (S), Q13.2 (S), Q14.2 (S), Q15.2 (S), Q16.2 (S), Q17.2 (S), Q18.2 (S), Q19.2 (S), Q20.2 (S), Q21.2 (S), Q22.2 (S), Q23.2 (S), Q24.2 (S), Q25.2 (S), Q26.2 (S), Q27.2 (S), Q28.2 (S), Q29.2 (S), Q30.2 (S), Q31.2 (S), Q32.2 (S), Q33.2 (S), Q34.2 (S), Q35.2 (S), Q36.2 (S), Q37.2 (S), Q38.2 (S), Q39.2 (S), Q40.2 (S), Q41.2 (S), Q42.2 (S), Q43.2 (S), Q44.2 (S), Q45.2 (S), Q46.2 (S), Q47.2 (S), Q48.2 (S), Q49.2 (S), Q50.2 (S), Q51.2 (S), Q52.2 (S), Q53.2 (S), Q54.2 (S), Q55.2 (S), Q56.2 (S), Q57.2 (S), Q58.2 (S), Q59.2 (S), Q60.2 (S), Q61.2 (S), Q62.2 (S), U5.8 (GND), U5.13 (~OE), U6.8 (GND), U6.13 (~OE), U7.8 (GND), U7.13 (~OE), U8.8 (GND), U8.13 (~OE), U9.8 (GND), U9.13 (~OE), U10.8 (GND), U10.13 (~OE), U11.8 (GND), U11.13 (~OE), U12.8 (GND), U12.13 (~OE); also elsewhere on the board
unnamed: N1.11 (A), R17.2
unnamed: N2.11 (A), R18.2
unnamed: N3.11 (A), R19.2
unnamed: N4.11 (A), R20.2
unnamed: N5.11 (A), R21.2
unnamed: N6.11 (A), R22.2

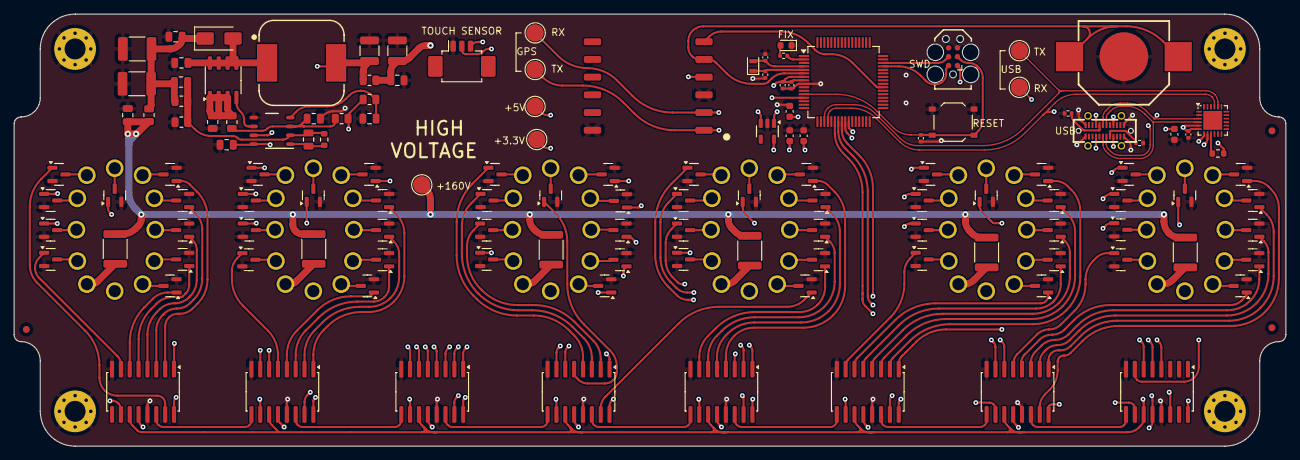
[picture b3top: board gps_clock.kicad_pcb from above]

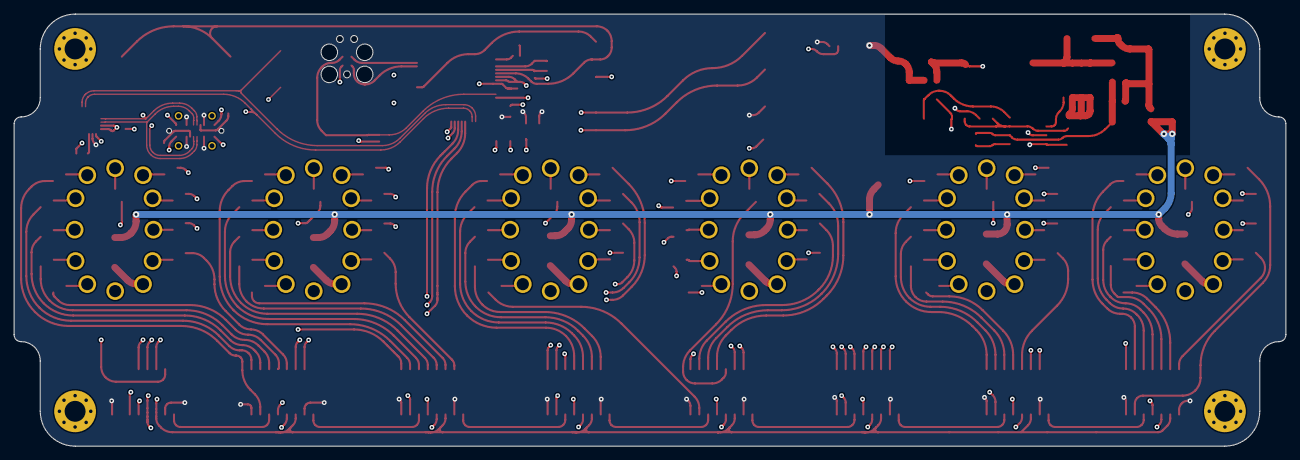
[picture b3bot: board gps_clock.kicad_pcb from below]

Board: 4 copper layers, 182.5 x 62.0 mm, 145 parts (6 on the bottom side), 169 nets.

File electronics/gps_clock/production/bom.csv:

Designator,Footprint,Quantity,Value,LCSC Part #
BT2,BAT-SMD_MY-1220-03,1,~,
"C1, C2, C24, C3",0603,4,4u7,
"C10, C15",1210,2,100uF 16v,EMK325ABJ107MM-P
C11,0805,1,0.1uF,C0805C104K3RACTU
C12,0805,1,220pF,C0805C221M5RACTU
C13,0805,1,430pF,CL21C431JBANNNC
C14,0805,1,0.1uF 16v,C0805C104K3RACTU
C16,0805,1,1nF,C0805C102M5RACTU
C17,0805,1,560pF 250v,C0603C561JAGAC7867
C18,0805,1,100pF 250v,C0805C101JAGAC7800
"C19, C20",1812,2,1uF 250v,C4532X7T2E105M250KE
"C21, C22",0805,2,0.1uF 250v,CGA4J3X7T2E104M125AE
"C23, C4, C6, C9",0402,4,100n,
"C5, C7",0402,2,10p,
D1,0603,1,LED,
D2,D_SMA,1,ES1D,ES1D
J1,Molex_PicoBlade_53261-0371_1x03-1MP_P1.25mm_Horizontal,1,Conn_01x03_Pin,
J3,USB-C-SMD_U263-241N-4BQC02,1,USB_C_Receptacle_USB2.0_14P,
"L1, L3",0805,2,60ohm 100Mhz,BKP2125HS600-T
L2,WE-PD_1210,1,33uH,7447709330
"Q10, Q11, Q12, Q13, Q14, Q15, Q16, Q17, Q18, Q19, Q20, Q21, Q22, Q23, Q24, Q25, Q26, Q27, Q28, Q29, Q3, Q30, Q31, Q32, Q33, Q34, Q35, Q36, Q37, Q38, Q39, Q4, Q40, Q41, Q42, Q43, Q44, Q45, Q46, Q47, Q48, Q49, Q5, Q50, Q51, Q52, Q53, Q54, Q55, Q56, Q57, Q58, Q59, Q6, Q60, Q61, Q62, Q7, Q8, Q9",SOT-23,60,BSS127S,
Q2,SOIC-8_3.9x4.9mm_P1.27mm,1,FDS2672CT,FDS2672CT-ND
"R1, R10",0603,2,10k,
R12,0805,1,4.12k,RC0805FR-074K12L
R13,0805,1,1k,RC0805FR-071KL
R14,0805,1,0.1 1/2W,ERJ-6DSFR10V
R15,0805,1,634k,RC0805FR-07634KL
R16,0805,1,7.68k,RC0805FR-077K68L
"R17, R18, R19, R20, R21, R22",1812,6,18k,
"R2, R5, R6",0402,3,5k1,
R9,0805,1,60.4k,RC0805FR-0760K4L
SW2,SW_Push_1P1T_XKB_TS-1187A,1,SW_Push,
U1,SOT-23-5,1,MIC5365-3.3YD5,
"U10, U11, U12, U5, U6, U7, U8, U9",SOIC-16W_5.3x10.2mm_P1.27mm,8,74HC595,
U2,QFN-24-1EP_4x4mm_P0.5mm_EP2.7x2.7mm,1,CP2104,
U3,LQFP-64_10x10mm_P0.5mm,1,STM32G070RBTx,
U4,D0008A_L,1,UCC3803,UCC3803DTR
X1,Crystal_SMD_2012-2Pin_2.0x1.2mm,1,32kHz768,
